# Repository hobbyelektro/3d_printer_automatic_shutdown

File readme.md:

# Automatic 3D printer shutdown

Documentation
--------------------
https://www.hobbyelektro.eu/automaticke-vypnuti-3d-tiskarny/

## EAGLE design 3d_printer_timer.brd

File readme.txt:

More details: https://www.hobbyelektro.eu/automaticke-vypnuti-3d-tiskarny/

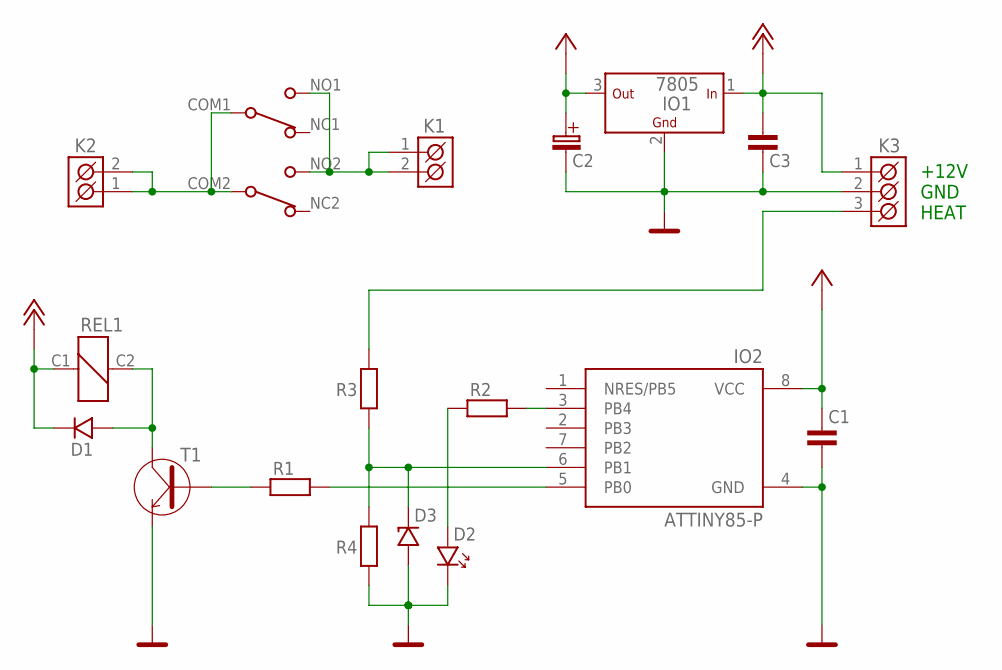
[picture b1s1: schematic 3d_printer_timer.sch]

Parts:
C1, C3: 100n; 1206
C2: 100u; C-EL_2,5
D1: 1N4148; DO35
D2: LED_3
D3: 5V1; DO35
IO1: 7805; TO-220S
IO2: ATTINY85-P; PDIP08_300MIL
K1, K2: ARK500/2
K3: ARK500/3
R1: 1k; R-10
R2: 330R; R-10
R3, R4: R_10; R-10
REL1: 40.52; RELEMZPA92
T1: BC546; TO-92

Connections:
+5V: C1.2, C2.C+ (C_EL+), IO1.3 (OUT), IO2.8 (VCC)
+12V: C3.2, D1.K, IO1.1 (IN), K3.1 (K1), REL1.C1
GND: C1.1, C2.C- (C_EL-), C3.1, D2.K, D3.A, IO1.2 (GND), IO2.4 (GND), K3.2 (K2), R4.1, T1.3 (E)
unnamed: K2.1 (K1), K2.2 (K2), REL1.COM1 (COM), REL1.COM2 (COM)
unnamed: K1.1 (K1), K1.2 (K2), REL1.NO1 (NO), REL1.NO2 (NO)
unnamed: D1.A, REL1.C2, T1.1 (C)
unnamed: R1.1, T1.2 (B)
unnamed: IO2.5 (PB0), R1.2
unnamed: IO2.3 (PB4), R2.2
unnamed: D2.A, R2.1
unnamed: D3.K, IO2.6 (PB1), R3.1, R4.2
unnamed: K3.3 (K3), R3.2

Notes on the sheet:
+12V GND HEAT

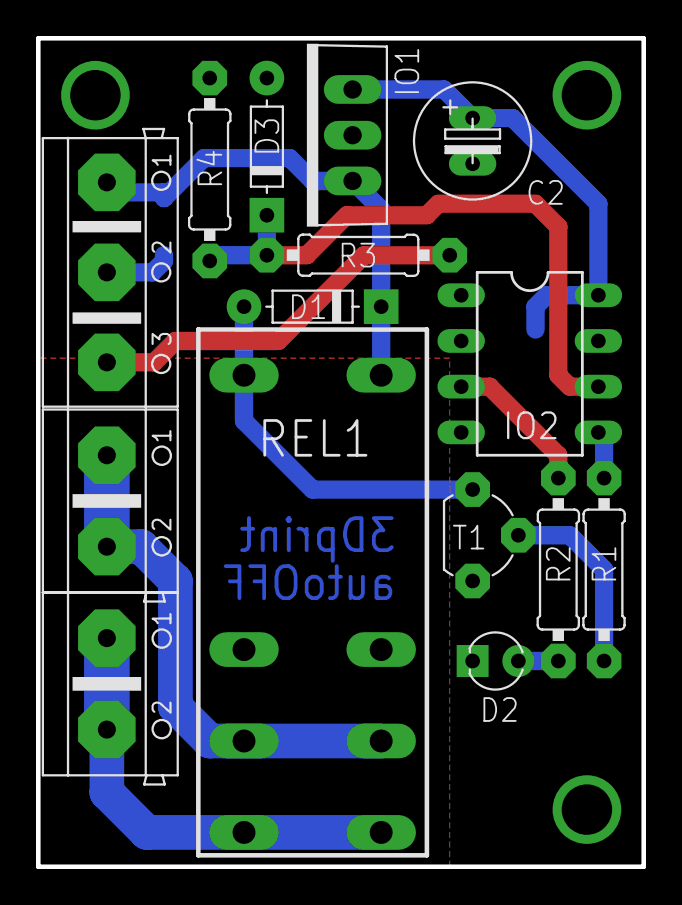
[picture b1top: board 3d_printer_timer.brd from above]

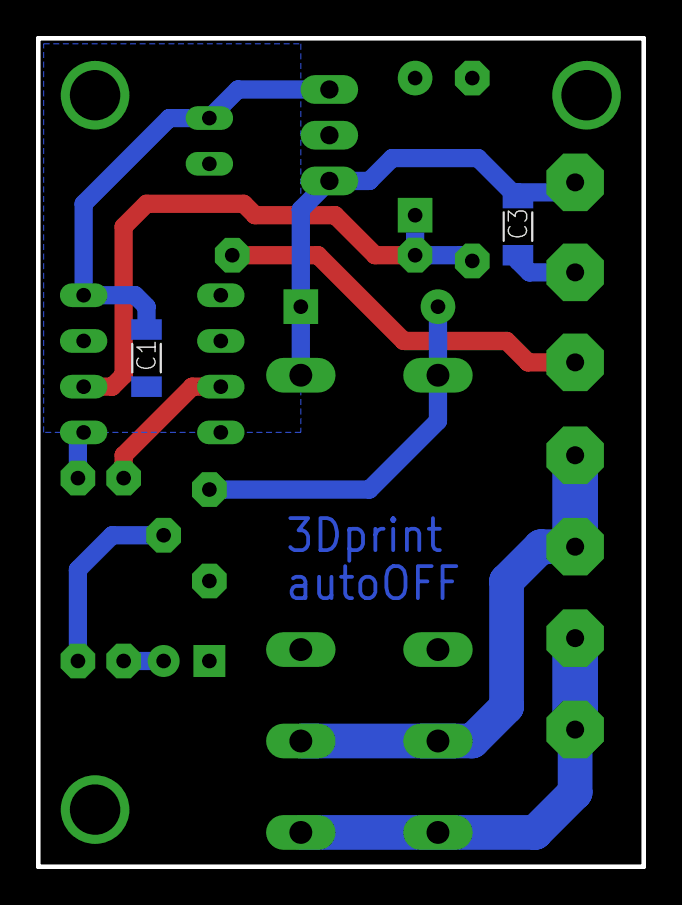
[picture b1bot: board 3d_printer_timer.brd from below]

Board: 2 copper layers, 33.6 x 46.0 mm, 17 parts (2 on the bottom side), 12 nets.

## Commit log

2020-11-19 3D printer auto shutdown
2020-11-19 Readme

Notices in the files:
parts and their libraries:
Copyright (C) PaJa 2001-2014
Copyright (C) PaJa 2011-2014
